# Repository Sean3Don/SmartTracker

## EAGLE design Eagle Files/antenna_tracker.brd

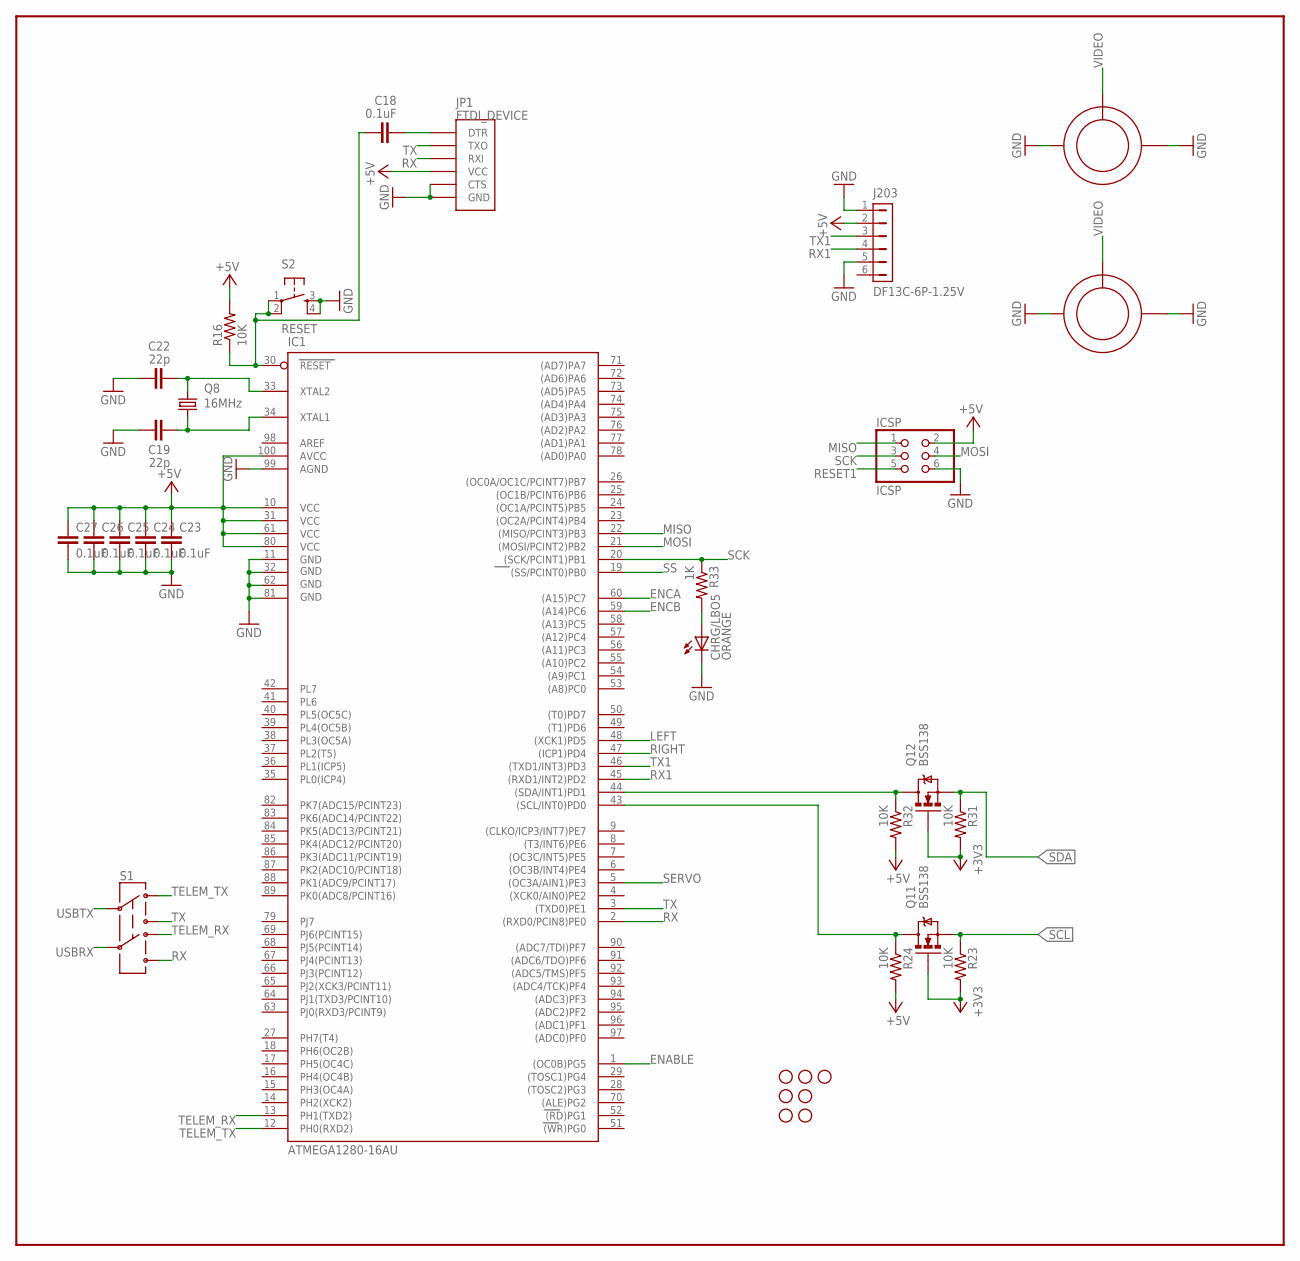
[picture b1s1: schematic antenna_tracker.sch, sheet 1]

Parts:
C18, C23, C24, C25, C26, C27: 0.1uF; C0603K; PARTNO GRM188R71E104KA01D
C19, C22: 22p; C0603K; PARTNO C0805C220J5GACTU
CHRG/LBO5: ORANGE; CHIP-LED0805; PARTNO APT2012SECK
IC1: ATMEGA1280-16AU; TQFP100
ICSP: ICSP; 2X03; PARTNO PPTC032LFBN-RC
J203: DF13C-6P-1.25V; PARTNO DF13C-6P-1.25V(20)
JP1: FTDI_DEVICE; FTDI_DEVICE_SIDE; PARTNO PREC040SFAN-RC
Q8: 16MHz; HC49/S; PARTNO ATS16B
Q11, Q12: BSS138; SOT23-3; PARTNO BSS138
R16, R23, R24, R31, R32: 10K; R0805; PARTNO 1623097-1
R33: 1K; M0805; PARTNO RMCF0805JT1K00
S1: SWITCH-DPDTPTH; MSS22; PARTNO 1825261-2
S2: RESET; TACTILE-PTH; PARTNO 1825910-6
STANDOFF1, STANDOFF2, STANDOFF3, STANDOFF4, STANDOFF5, STANDOFF6, STANDOFF7: STAND-OFF
U$10, U$11: RCA_VERTICAL; PARTNO RCJ-021

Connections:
+3V3: Q11.1 (G), Q12.1 (G), R23.2, R31.2; also elsewhere on the board
+5V: C23.1, C24.1, C25.1, C26.1, C27.1, IC1.10 (VCC), IC1.31 (VCC1), IC1.61 (VCC2), IC1.80 (VCC3), IC1.100 (AVCC), ICSP.2, J203.2, JP1.P$4 (VCC), R16.2, R24.2, R32.2; also elsewhere on the board
ENABLE: IC1.1 ((OC0B)PG5); also elsewhere on the board
ENCA: IC1.60 ((A15)PC7); also elsewhere on the board
ENCB: IC1.59 ((A14)PC6); also elsewhere on the board
GND: C19.1, C22.1, C23.2, C24.2, C25.2, C26.2, C27.2, CHRG/LBO5.C, IC1.11 (GND), IC1.32 (GND1), IC1.62 (GND2), IC1.81 (GND3), IC1.99 (AGND), ICSP.6, J203.1, J203.5, JP1.P$5 (CTS), JP1.P$6 (GND), S2.3, S2.4, U$10.P$1 (GND), U$10.P$2 (GND), U$11.P$1 (GND), U$11.P$2 (GND); also elsewhere on the board
LEFT: IC1.48 ((XCK1)PD5); also elsewhere on the board
MISO: IC1.22 ((MISO/PCINT3)PB3), ICSP.1
MOSI: IC1.21 ((MOSI/PCINT2)PB2), ICSP.4
unnamed: C18.2, JP1.P$1 (DTR)
unnamed: C19.2, IC1.34 (XTAL1), Q8.1
unnamed: C22.2, IC1.33 (XTAL2), Q8.2
unnamed: IC1.44 ((SDA/INT1)PD1), Q12.3 (D), R32.1
unnamed: IC1.43 ((SCL/INT0)PD0), Q11.3 (D), R24.1
unnamed: CHRG/LBO5.A, R33.2
RESET1: C18.1, IC1.30 (RESET), ICSP.5, R16.1, S2.1, S2.2
RIGHT: IC1.47 ((ICP1)PD4); also elsewhere on the board
RX: IC1.2 ((RXD0/PCIN8)PE0), JP1.P$3 (RXI), S1.6
RX1: IC1.45 ((RXD1/INT2)PD2), J203.4
SCK: IC1.20 ((SCK/PCINT1)PB1), ICSP.3, R33.1
SCL: Q11.2 (S), R23.1; also elsewhere on the board
SDA: Q12.2 (S), R31.1; also elsewhere on the board
SERVO: IC1.5 ((OC3A/AIN1)PE3); also elsewhere on the board
SS: IC1.19 ((SS/PCINT0)PB0)
TELEM_RX: IC1.13 (PH1(TXD2)), S1.4; also elsewhere on the board
TELEM_TX: IC1.12 (PH0(RXD2)), S1.1; also elsewhere on the board
TX: IC1.3 ((TXD0)PE1), JP1.P$2 (TXO), S1.3
TX1: IC1.46 ((TXD1/INT3)PD3), J203.3
USBRX: S1.5; also elsewhere on the board
USBTX: S1.2; also elsewhere on the board
VIDEO: U$10.P$3 (SIGNAL), U$11.P$3 (SIGNAL); also elsewhere on the board

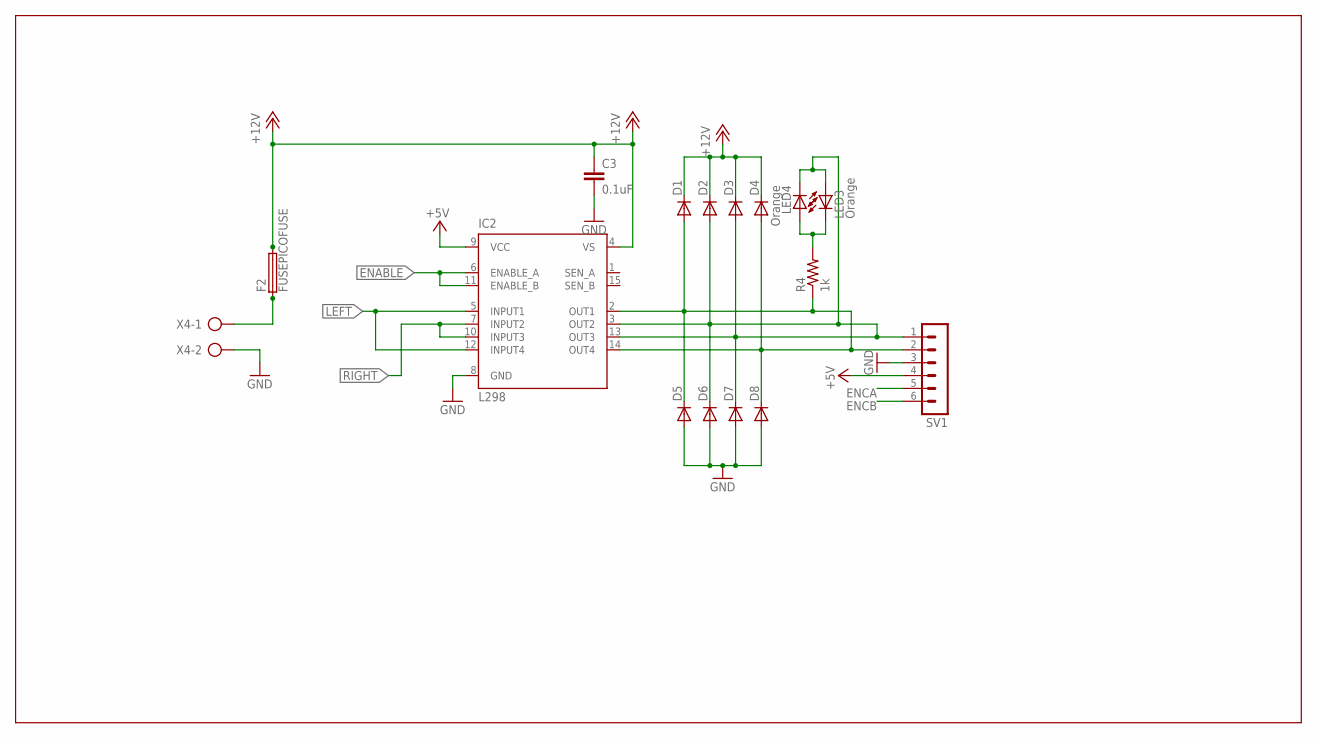
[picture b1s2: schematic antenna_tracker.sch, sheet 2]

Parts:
C3: 0.1uF; 0603-CAP; PARTNO GRM188R71E104KA01D
D1, D2, D3, D4, D5, D6, D7, D8: DIODE-DO214AC; DO214AC; PARTNO ES2B-LTP
F2: FUSEPICOFUSE; PICOFUSE; PARTNO RUEF700-2
IC2: L298; MULTIWATT-15
LED3, LED4: Orange; SML0805; PARTNO APT2012SECK
R4: 1k; R0805; PARTNO RMCF0805JT1K00
SV1: MA06-1; PARTNO PREC040SFAN-RC
X4: AK300/2; PARTNO OSTTC022162

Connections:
+5V: IC2.9 (VCC), SV1.4; also elsewhere on the board
+12V: C3.1, D1.C, D2.C, D3.C, D4.C, F2.2, IC2.4 (VS); also elsewhere on the board
ENABLE: IC2.6 (ENABLE_A), IC2.11 (ENABLE_B); also elsewhere on the board
ENCA: SV1.5; also elsewhere on the board
ENCB: SV1.6; also elsewhere on the board
GND: C3.2, D5.A, D6.A, D7.A, D8.A, IC2.8 (GND), SV1.3, X4.2; also elsewhere on the board
LEFT: IC2.5 (INPUT1), IC2.12 (INPUT4); also elsewhere on the board
unnamed: D2.A, D3.A, D6.C, D7.C, IC2.3 (OUT2), IC2.13 (OUT3), LED3.A, LED4.C, SV1.1
unnamed: D1.A, D4.A, D5.C, D8.C, IC2.2 (OUT1), IC2.14 (OUT4), R4.1, SV1.2
unnamed: LED3.C, LED4.A, R4.2
unnamed: F2.1, X4.1
RIGHT: IC2.7 (INPUT2), IC2.10 (INPUT3); also elsewhere on the board

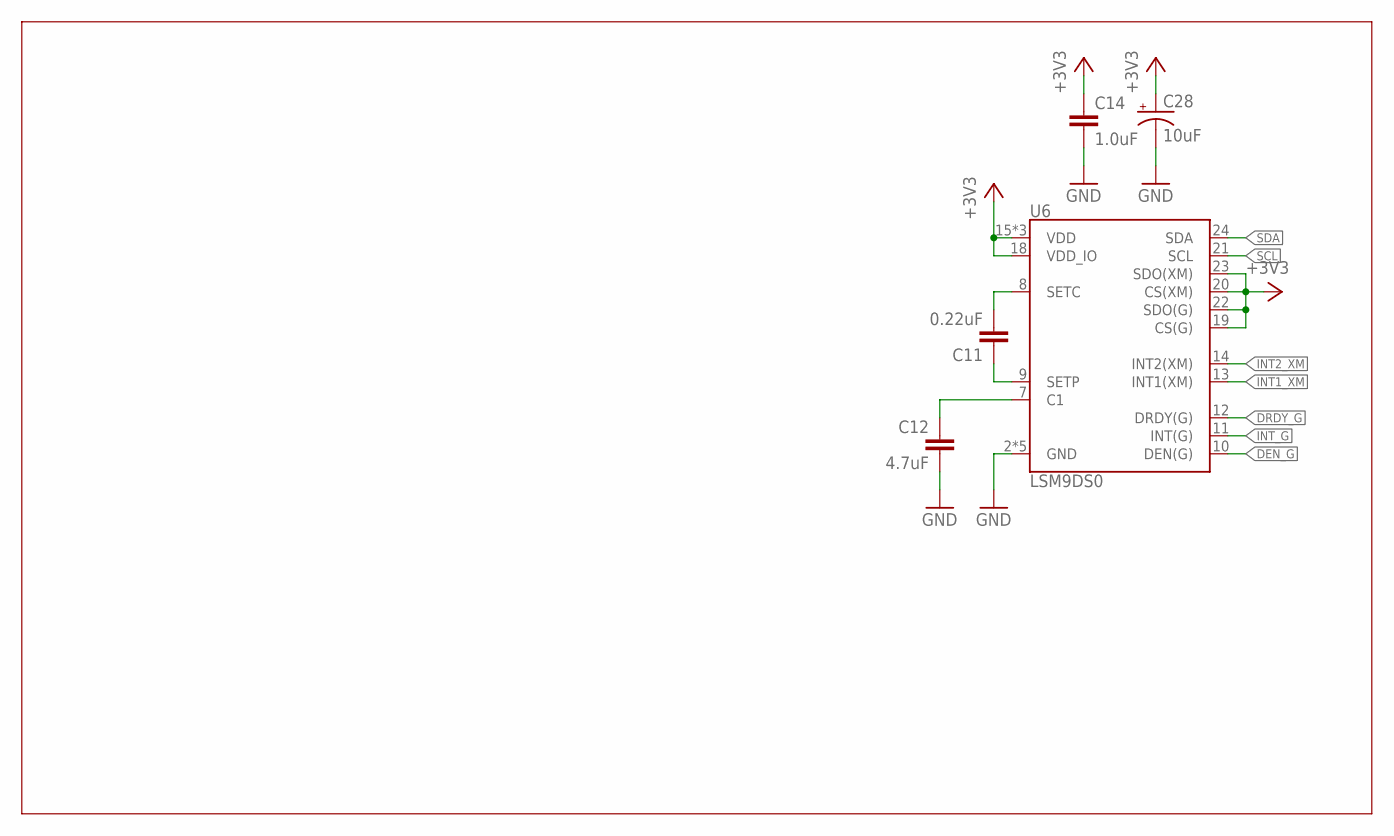
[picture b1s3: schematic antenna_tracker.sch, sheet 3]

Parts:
C11: 0.22uF; 0603-CAP; PARTNO CL10B224KA8NNNC
C12: 4.7uF; 0603-CAP; PARTNO CL10B475KQ8NQNC
C14: 1.0uF; 0603-CAP; PARTNO C0603C105K8PACTU
C28: 10uF; EIA3216; PARTNO EEE-1CA100SR
U6: LSM9DS0; LGA-24

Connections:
+3V3: C14.1, C28.A (+), U6.15 (VDD), U6.16 (VDD), U6.17 (VDD), U6.18 (VDD_IO), U6.19 (CS(G)), U6.20 (CS(XM)), U6.22 (SDO(G)), U6.23 (SDO(XM)); also elsewhere on the board
DEN_G: U6.10 (DEN(G))
DRDY_G: U6.12 (DRDY(G))
GND: C12.2, C14.2, C28.C (-), U6.2 (GND), U6.3 (GND), U6.4 (GND), U6.5 (GND), U6.6 (GND); also elsewhere on the board
INT1_XM: U6.13 (INT1(XM))
INT2_XM: U6.14 (INT2(XM))
INT_G: U6.11 (INT(G))
unnamed: C11.1, U6.9 (SETP)
unnamed: C11.2, U6.8 (SETC)
unnamed: C12.1, U6.7 (C1)
SCL: U6.21 (SCL); also elsewhere on the board
SDA: U6.24 (SDA); also elsewhere on the board

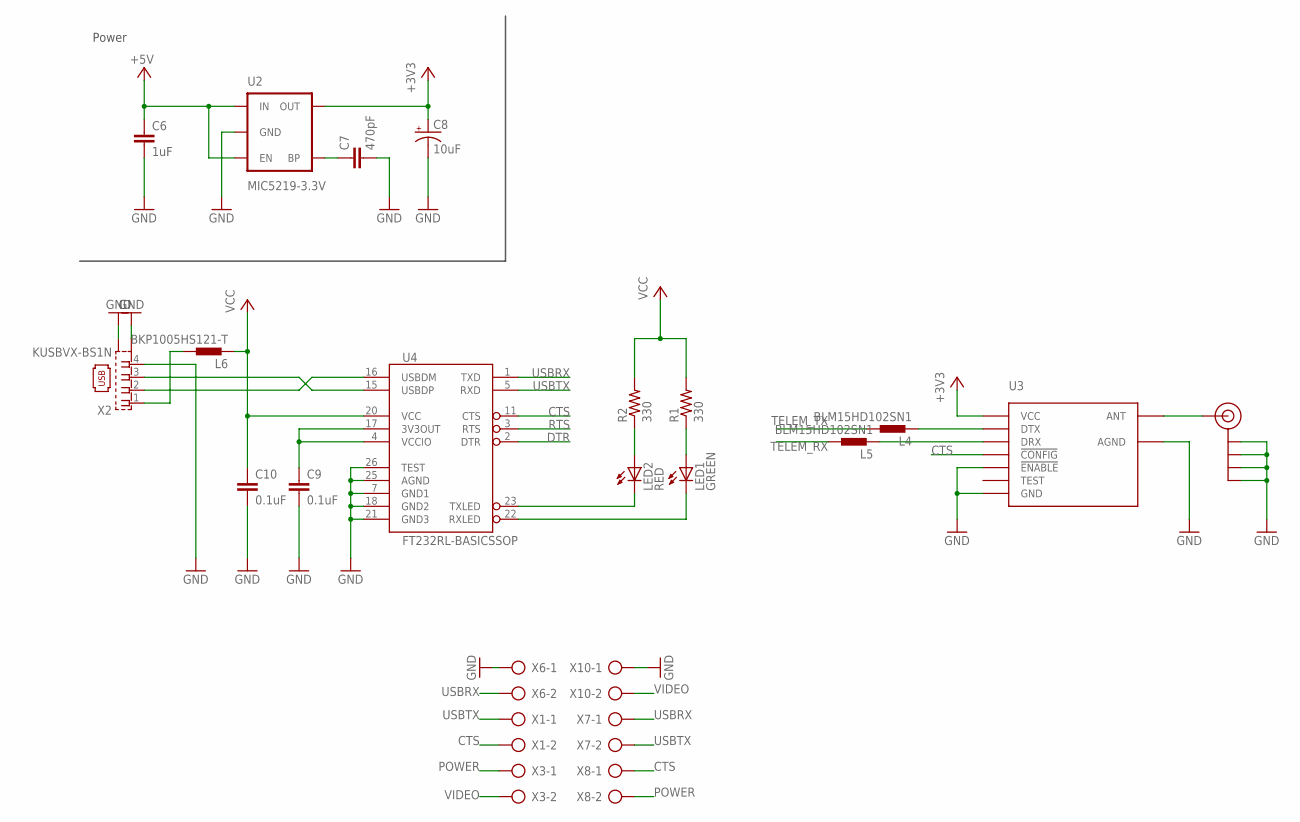
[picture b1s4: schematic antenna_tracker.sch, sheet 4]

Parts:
C6: 1uF; 0402-CAP; PARTNO C0603C105K8PACTU
C7: 470pF; 0402-CAP; PARTNO GRM1555C1H471JA01D
C8: 10uF; EIA3216; PARTNO EEE-1CA100SR
C9, C10: 0.1uF; C0603K; PARTNO GRM188R71E104KA01D
J$1: SMA_EDGE; SMA-EDGE; PARTNO 0732511150
L4, L5: BLM15HD102SN1; 0402-IND; PARTNO BLM15HD102SN1D
L6: BKP1005HS121-T; 0402-IND; PARTNO BKP1005HS121-T
LED1: GREEN; CHIP-LED0805; PARTNO LG R971-KN-1
LED2: RED; CHIP-LED0805; PARTNO LH R974-LP-1
R1, R2: 330; 0402-RES; PARTNO MCR01MRTF3300
U2: MIC5219-3.3V; SOT23-5; PARTNO MIC5219-3.3YM5 TR
U3: HM-TRPSMD; HM-TRP-SMD
U4: FT232RL-BASICSSOP; SSOP28DB; PARTNO FT232RL-REEL
X1, X3, X6, X7, X8, X10: AK300/2; PARTNO OSTTC022162
X2: KUSBVX-BS1N; PARTNO 5787834-1

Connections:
+3V3: C8.A (+), U2.5 (OUT), U3.VCC; also elsewhere on the board
+5V: C6.1, U2.1 (IN), U2.3 (EN); also elsewhere on the board
CTS: U3.!CONFIG, U4.11 (CTS), X1.2, X8.1
DTR: U4.2 (DTR)
GND: C6.2, C7.2, C8.C (-), C9.2, C10.2, J$1.GND@0 (GND), J$1.GND@1 (GND), J$1.GND@2 (GND), J$1.GND@3 (GND), U2.2 (GND), U3.!ENABLE, U3.AGND, U3.GND, U4.7 (GND1), U4.18 (GND2), U4.21 (GND3), U4.25 (AGND), U4.26 (TEST), X2.4, X2.M1 (S1), X2.M2 (S2), X6.1, X10.1; also elsewhere on the board
unnamed: C7.1, U2.4 (BP)
unnamed: J$1.SIG (SIGNAL), U3.ANT
unnamed: C9.1, U4.4 (VCCIO), U4.17 (3V3OUT)
unnamed: U4.16 (USBDM), X2.2
unnamed: LED2.A, R2.1
unnamed: LED1.A, R1.1
unnamed: LED2.C, U4.23 (TXLED)
unnamed: LED1.C, U4.22 (RXLED)
unnamed: L4.P$2 (2), U3.DTX
unnamed: L5.P$2 (2), U3.DRX
unnamed: L6.P$1 (1), X2.1
unnamed: U4.15 (USBDP), X2.3
POWER: X3.1, X8.2
RTS: U4.3 (RTS)
TELEM_RX: L5.P$1 (1); also elsewhere on the board
TELEM_TX: L4.P$1 (1); also elsewhere on the board
USBRX: U4.1 (TXD), X6.2, X7.1; also elsewhere on the board
USBTX: U4.5 (RXD), X1.1, X7.2; also elsewhere on the board
VCC: C10.1, L6.P$2 (2), R1.2, R2.2, U4.20 (VCC)
VIDEO: X3.2, X10.2; also elsewhere on the board

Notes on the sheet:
Power

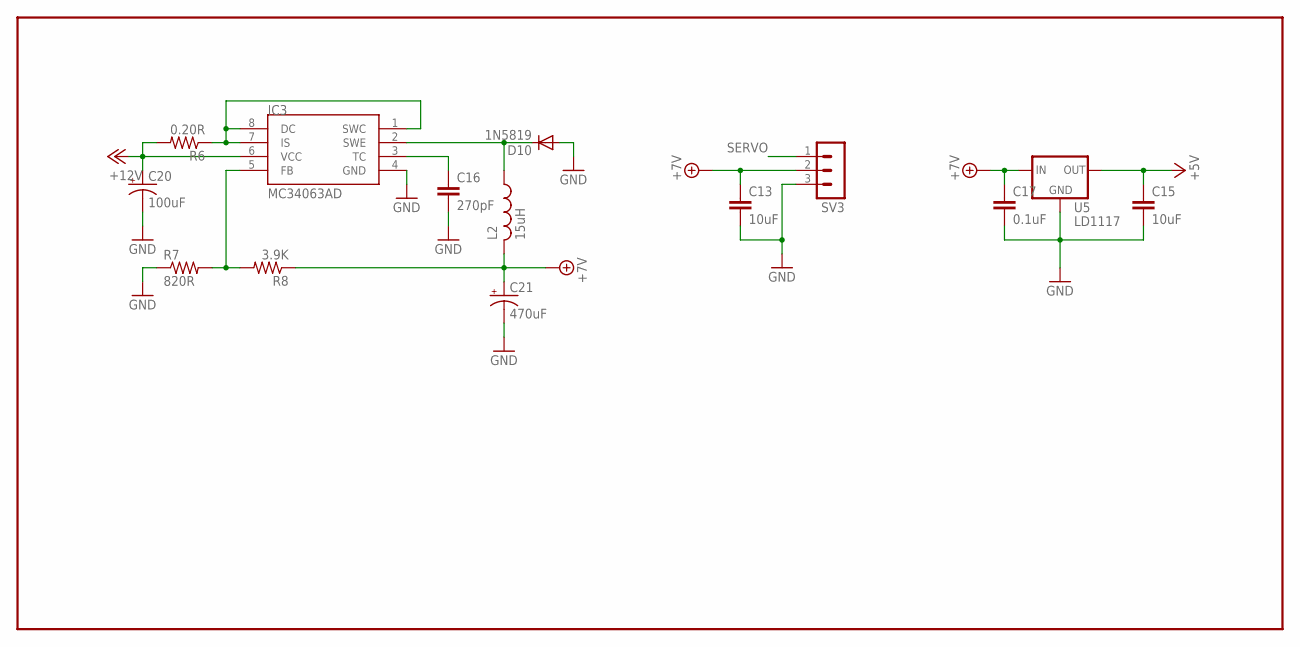
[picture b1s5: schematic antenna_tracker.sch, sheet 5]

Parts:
C13, C15: 10uF; C0805K; PARTNO CL21A106KAFN3NE
C16: 270pF; C0603K; PARTNO CC0603KRX7R9BB271
C17: 0.1uF; C0603K; PARTNO GRM188R71E104KA01D
C20: 100uF; E2,5-6E; PARTNO ESK107M025AE3AA
C21: 470uF; E3,5-8; PARTNO UVR1C471MPD
D10: 1N5819; SOD123; PARTNO 1N5819HW-7-F
IC3: MC34063AD; SOIC8; PARTNO MC34063ECD-TR
L2: 15uH; POWER-CHOKE_WE-TPC; PARTNO NR6028T150M
R6: 0.20R; R0603; PARTNO 73L2R20J
R7: 820R; R0603; PARTNO 1623097-1
R8: 3.9K; R0603; PARTNO RMCF0603JT3K90
SV3: MA03-1; PARTNO PREC040SFAN-RC
U5: LD1117; DPAK; PARTNO LD1117DT50CTR

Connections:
+5V: C15.1, U5.4 (OUT); also elsewhere on the board
+7V: C13.1, C17.1, C21.+, L2.2, R8.1, SV3.2, U5.3 (IN)
+12V: C20.+, IC3.6 (VCC), R6.2; also elsewhere on the board
GND: C13.2, C15.2, C16.2, C17.2, C20.-, C21.-, D10.A, IC3.4 (GND), R7.1, SV3.3, U5.1 (GND); also elsewhere on the board
unnamed: C16.1, IC3.3 (TC)
unnamed: IC3.1 (SWC), IC3.7 (IS), IC3.8 (DC), R6.1
unnamed: IC3.5 (FB), R7.2, R8.2
unnamed: D10.C, IC3.2 (SWE), L2.1
SERVO: SV3.1; also elsewhere on the board

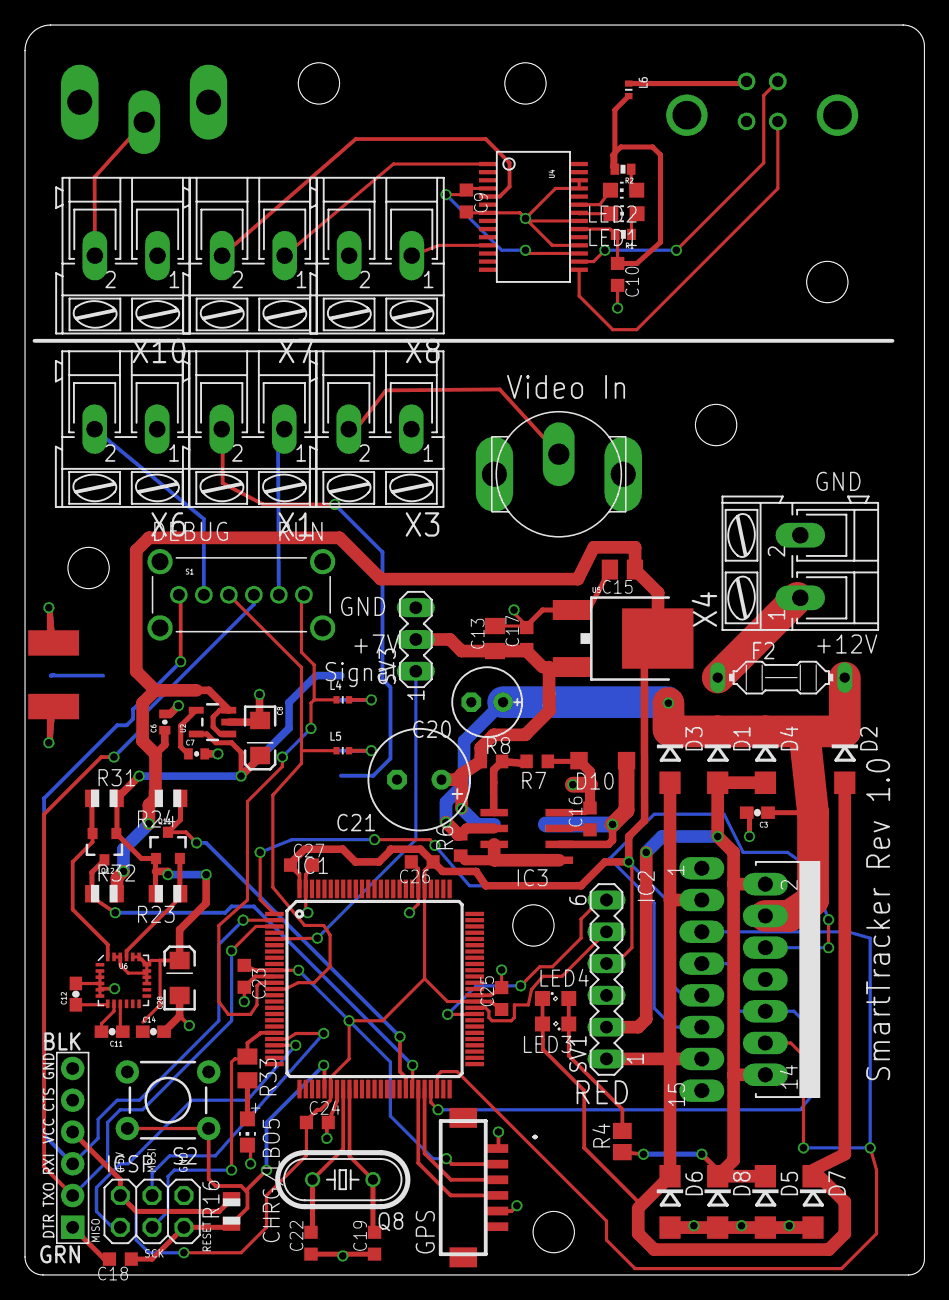
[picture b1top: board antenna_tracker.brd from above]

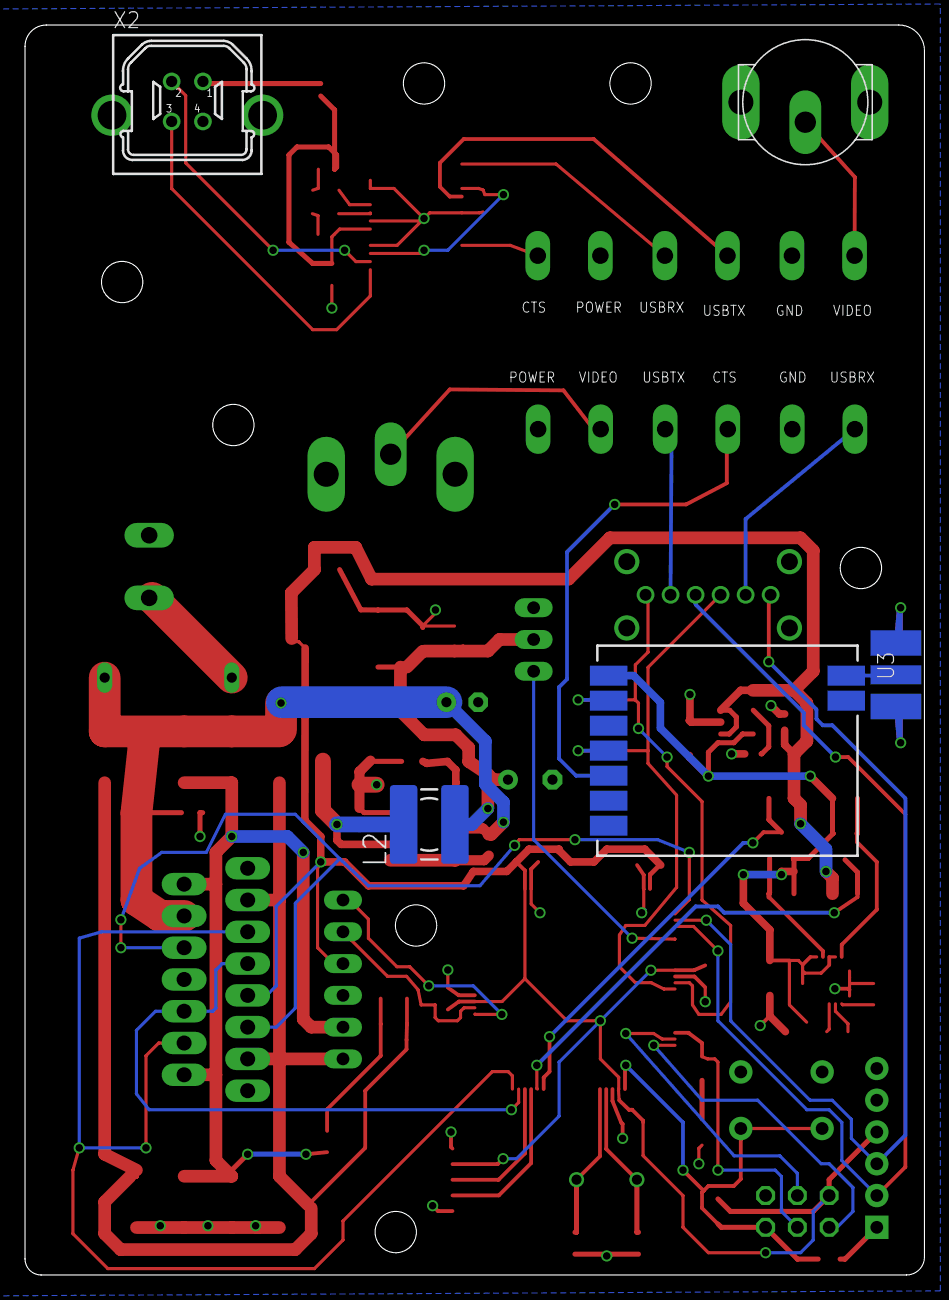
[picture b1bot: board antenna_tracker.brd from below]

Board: 4 copper layers, 71.9 x 99.9 mm, 91 parts (5 on the bottom side), 58 nets.

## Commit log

2014-05-14 First Commit
    First Commit - Demonstrated receiving telemetry over MAVLink
2014-05-18 Added angle calculations
    Added getAzimuth, getInclination & setHome
2014-08-01 Eagle Files
    Added the .brd and .sch files for the controller
2014-08-04 Switched to 9DOF IC and a new 7.2V Buck Convertor
    Added LSM9DS0 and MC34063
2015-03-30 Added Solidworks Parts
    Added Solidworks parts and assembly

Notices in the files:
parts and their libraries:
SparkFun-Electromechanical: Licensing: CC v3.0 Share-Alike You are welcome to use this library for commercial purposes.
SparkFun-Capacitors: Licensing: Creative Commons ShareAlike 4.0 International - https://creativecommons.org/licenses/by-sa/4.0
